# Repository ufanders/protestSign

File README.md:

protestSign
===========

A 25x7 pixel scanned-matrix display using 10mm LEDs

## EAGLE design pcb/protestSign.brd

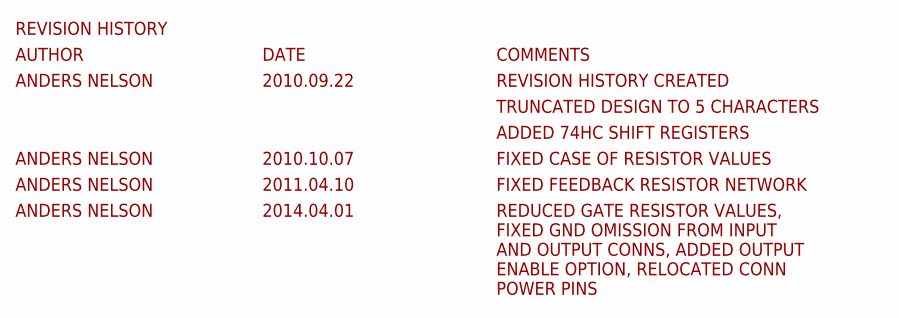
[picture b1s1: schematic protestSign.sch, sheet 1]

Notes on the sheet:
REVISION HISTORY
AUTHOR
DATE
COMMENTS
ANDERS NELSON
2010.09.22
REVISION HISTORY CREATED
TRUNCATED DESIGN TO 5 CHARACTERS
ADDED 74HC SHIFT REGISTERS
2010.10.07
FIXED CASE OF RESISTOR VALUES
2011.04.10
FIXED FEEDBACK RESISTOR NETWORK
2014.04.01
REDUCED GATE RESISTOR VALUES, FIXED GND OMISSION FROM INPUT AND OUTPUT CONNS, ADDED OUTPUT ENABLE OPTION, RELOCATED CONN POWER PINS

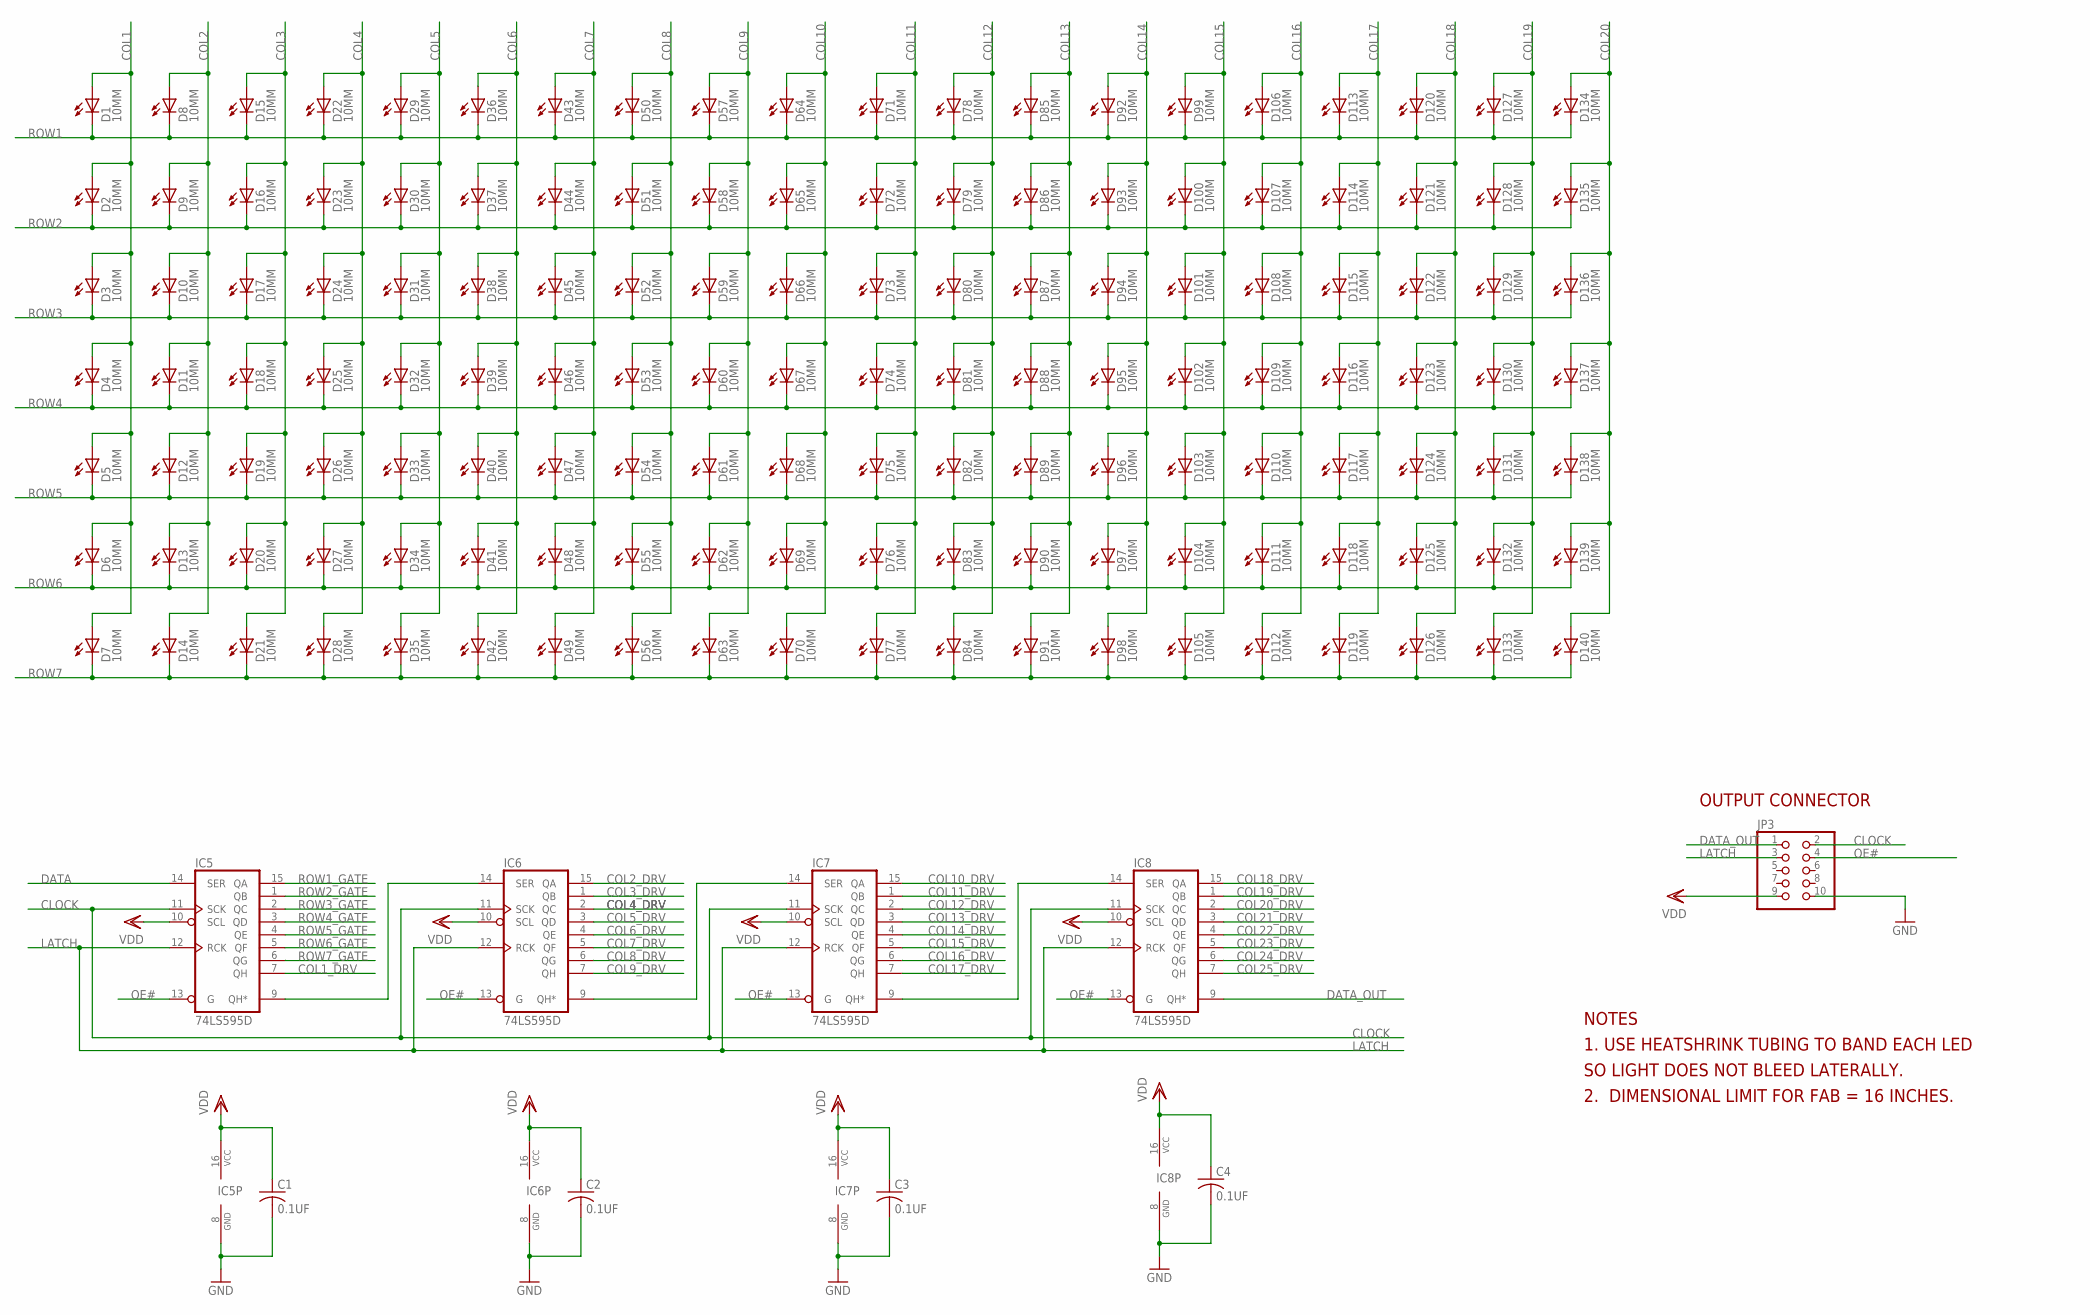
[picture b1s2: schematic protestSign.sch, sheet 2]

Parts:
C1, C2, C3, C4: 0.1UF; C0603
D1, D2, D3, D4, D5, D6, D7, D8, D9, D10, D11, D12, D13, D14, D15, D16, D17, D18, D19, D20, D21, D22, D23, D24, D25, D26, D27, D28, D29, D30, D31, D32, D33, D34, D35, D36, D37, D38, D39, D40, D41, D42, D43, D44, D45, D46, D47, D48, D49, D50, D51, D52, D53, D54, D55, D56, D57, D58, D59, D60, D61, D62, D63, D64, D65, D66, D67, D68, D69, D70, D71, D72, D73, D74, D75, D76, D77, D78, D79, D80, D81, D82, D83, D84, D85, D86, D87, D88, D89, D90, D91, D92, D93, D94, D95, D96, D97, D98, D99, D100, D101, D102, D103, D104, D105, D106, D107, D108, D109, D110, D111, D112, D113, D114, D115, D116, D117, D118, D119, D120, D121, D122, D123, D124, D125, D126, D127, D128, D129, D130, D131, D132, D133, D134, D135, D136, D137, D138, D139, D140: 10MM; LED_10MM
IC5, IC6, IC7, IC8: 74LS595D; SO16
JP3: PINHD-2X5; 2X05

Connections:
CLOCK: IC5.11 (SCK), IC6.11 (SCK), IC7.11 (SCK), IC8.11 (SCK), JP3.2; also elsewhere on the board
COL1: D1.A, D2.A, D3.A, D4.A, D5.A, D6.A, D7.A; also elsewhere on the board
COL1_DRV: IC5.7 (QH); also elsewhere on the board
COL2: D8.A, D9.A, D10.A, D11.A, D12.A, D13.A, D14.A; also elsewhere on the board
COL2_DRV: IC6.15 (QA); also elsewhere on the board
COL3: D15.A, D16.A, D17.A, D18.A, D19.A, D20.A, D21.A; also elsewhere on the board
COL3_DRV: IC6.1 (QB); also elsewhere on the board
COL4: D22.A, D23.A, D24.A, D25.A, D26.A, D27.A, D28.A; also elsewhere on the board
COL4_DRV: IC6.2 (QC); also elsewhere on the board
COL5: D29.A, D30.A, D31.A, D32.A, D33.A, D34.A, D35.A; also elsewhere on the board
COL5_DRV: IC6.3 (QD); also elsewhere on the board
COL6: D36.A, D37.A, D38.A, D39.A, D40.A, D41.A, D42.A; also elsewhere on the board
COL6_DRV: IC6.4 (QE); also elsewhere on the board
COL7: D43.A, D44.A, D45.A, D46.A, D47.A, D48.A, D49.A; also elsewhere on the board
COL7_DRV: IC6.5 (QF); also elsewhere on the board
COL8: D50.A, D51.A, D52.A, D53.A, D54.A, D55.A, D56.A; also elsewhere on the board
COL8_DRV: IC6.6 (QG); also elsewhere on the board
COL9: D57.A, D58.A, D59.A, D60.A, D61.A, D62.A, D63.A; also elsewhere on the board
COL9_DRV: IC6.7 (QH); also elsewhere on the board
COL10: D64.A, D65.A, D66.A, D67.A, D68.A, D69.A, D70.A; also elsewhere on the board
COL10_DRV: IC7.15 (QA); also elsewhere on the board
COL11: D71.A, D72.A, D73.A, D74.A, D75.A, D76.A, D77.A; also elsewhere on the board
COL11_DRV: IC7.1 (QB); also elsewhere on the board
COL12: D78.A, D79.A, D80.A, D81.A, D82.A, D83.A, D84.A; also elsewhere on the board
COL12_DRV: IC7.2 (QC); also elsewhere on the board
COL13: D85.A, D86.A, D87.A, D88.A, D89.A, D90.A, D91.A; also elsewhere on the board
COL13_DRV: IC7.3 (QD); also elsewhere on the board
COL14: D92.A, D93.A, D94.A, D95.A, D96.A, D97.A, D98.A; also elsewhere on the board
COL14_DRV: IC7.4 (QE); also elsewhere on the board
COL15: D99.A, D100.A, D101.A, D102.A, D103.A, D104.A, D105.A; also elsewhere on the board
COL15_DRV: IC7.5 (QF); also elsewhere on the board
COL16: D106.A, D107.A, D108.A, D109.A, D110.A, D111.A, D112.A; also elsewhere on the board
COL16_DRV: IC7.6 (QG); also elsewhere on the board
COL17: D113.A, D114.A, D115.A, D116.A, D117.A, D118.A, D119.A; also elsewhere on the board
COL17_DRV: IC7.7 (QH); also elsewhere on the board
COL18: D120.A, D121.A, D122.A, D123.A, D124.A, D125.A, D126.A; also elsewhere on the board
COL18_DRV: IC8.15 (QA); also elsewhere on the board
COL19: D127.A, D128.A, D129.A, D130.A, D131.A, D132.A, D133.A; also elsewhere on the board
COL19_DRV: IC8.1 (QB); also elsewhere on the board
COL20: D134.A, D135.A, D136.A, D137.A, D138.A, D139.A, D140.A; also elsewhere on the board
COL20_DRV: IC8.2 (QC); also elsewhere on the board
COL21_DRV: IC8.3 (QD); also elsewhere on the board
COL22_DRV: IC8.4 (QE); also elsewhere on the board
COL23_DRV: IC8.5 (QF); also elsewhere on the board
COL24_DRV: IC8.6 (QG); also elsewhere on the board
COL25_DRV: IC8.7 (QH); also elsewhere on the board
DATA: IC5.14 (SER); also elsewhere on the board
DATA_OUT: IC8.9 (QH*), JP3.1
GND: C1.2, C2.2, C3.2, C4.2, IC5.8 (GND), IC6.8 (GND), IC7.8 (GND), IC8.8 (GND), JP3.10; also elsewhere on the board
LATCH: IC5.12 (RCK), IC6.12 (RCK), IC7.12 (RCK), IC8.12 (RCK), JP3.3; also elsewhere on the board
unnamed: IC5.9 (QH*), IC6.14 (SER)
unnamed: IC6.9 (QH*), IC7.14 (SER)
unnamed: IC7.9 (QH*), IC8.14 (SER)
OE#: IC5.13 (G), IC6.13 (G), IC7.13 (G), IC8.13 (G), JP3.4; also elsewhere on the board
ROW1: D1.C, D8.C, D15.C, D22.C, D29.C, D36.C, D43.C, D50.C, D57.C, D64.C, D71.C, D78.C, D85.C, D92.C, D99.C, D106.C, D113.C, D120.C, D127.C, D134.C; also elsewhere on the board
ROW1_GATE: IC5.15 (QA); also elsewhere on the board
ROW2: D2.C, D9.C, D16.C, D23.C, D30.C, D37.C, D44.C, D51.C, D58.C, D65.C, D72.C, D79.C, D86.C, D93.C, D100.C, D107.C, D114.C, D121.C, D128.C, D135.C; also elsewhere on the board
ROW2_GATE: IC5.1 (QB); also elsewhere on the board
ROW3: D3.C, D10.C, D17.C, D24.C, D31.C, D38.C, D45.C, D52.C, D59.C, D66.C, D73.C, D80.C, D87.C, D94.C, D101.C, D108.C, D115.C, D122.C, D129.C, D136.C; also elsewhere on the board
ROW3_GATE: IC5.2 (QC); also elsewhere on the board
ROW4: D4.C, D11.C, D18.C, D25.C, D32.C, D39.C, D46.C, D53.C, D60.C, D67.C, D74.C, D81.C, D88.C, D95.C, D102.C, D109.C, D116.C, D123.C, D130.C, D137.C; also elsewhere on the board
ROW4_GATE: IC5.3 (QD); also elsewhere on the board
ROW5: D5.C, D12.C, D19.C, D26.C, D33.C, D40.C, D47.C, D54.C, D61.C, D68.C, D75.C, D82.C, D89.C, D96.C, D103.C, D110.C, D117.C, D124.C, D131.C, D138.C; also elsewhere on the board
ROW5_GATE: IC5.4 (QE); also elsewhere on the board
ROW6: D6.C, D13.C, D20.C, D27.C, D34.C, D41.C, D48.C, D55.C, D62.C, D69.C, D76.C, D83.C, D90.C, D97.C, D104.C, D111.C, D118.C, D125.C, D132.C, D139.C; also elsewhere on the board
ROW6_GATE: IC5.5 (QF); also elsewhere on the board
ROW7: D7.C, D14.C, D21.C, D28.C, D35.C, D42.C, D49.C, D56.C, D63.C, D70.C, D77.C, D84.C, D91.C, D98.C, D105.C, D112.C, D119.C, D126.C, D133.C, D140.C; also elsewhere on the board
ROW7_GATE: IC5.6 (QG); also elsewhere on the board
VDD: C1.1, C2.1, C3.1, C4.1, IC5.10 (SCL), IC5.16 (VCC), IC6.10 (SCL), IC6.16 (VCC), IC7.10 (SCL), IC7.16 (VCC), IC8.10 (SCL), IC8.16 (VCC), JP3.9; also elsewhere on the board

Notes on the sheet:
NOTES
1. USE HEATSHRINK TUBING TO BAND EACH LED
SO LIGHT DOES NOT BLEED LATERALLY.
2. DIMENSIONAL LIMIT FOR FAB = 16 INCHES.
OUTPUT CONNECTOR

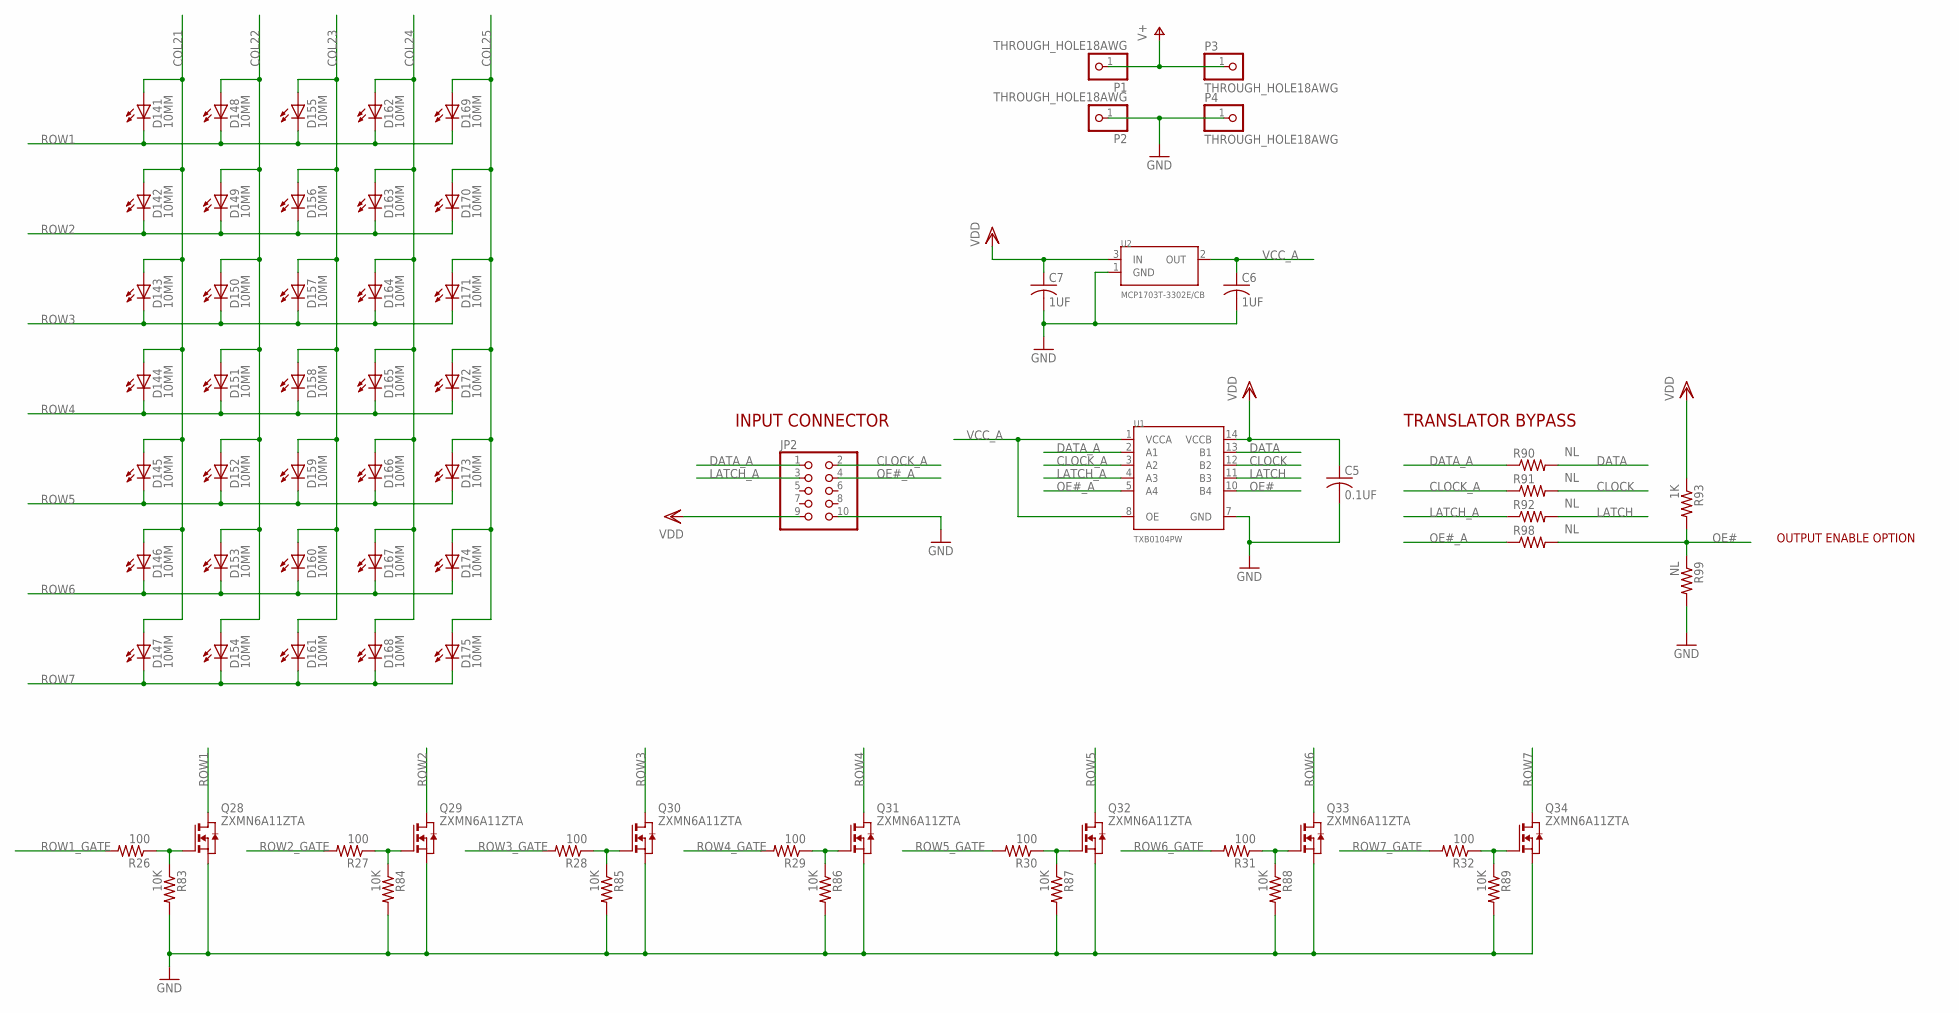
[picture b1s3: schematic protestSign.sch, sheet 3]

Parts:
C5: 0.1UF; C0603
C6, C7: 1UF; C0603
D141, D142, D143, D144, D145, D146, D147, D148, D149, D150, D151, D152, D153, D154, D155, D156, D157, D158, D159, D160, D161, D162, D163, D164, D165, D166, D167, D168, D169, D170, D171, D172, D173, D174, D175: 10MM; LED_10MM
JP2: PINHD-2X5; 2X05
P1, P2, P3, P4: THROUGH_HOLE18AWG; 18AWG_TH
Q28, Q29, Q30, Q31, Q32, Q33, Q34: ZXMN6A11ZTA; SOT89
R26, R27, R28, R29, R30, R31, R32: 100; R0603
R83, R84, R85, R86, R87, R88, R89: 10K; R0603
R90, R91, R92, R98, R99: NL; R0603
R93: 1K; R0603
U1: TXB0104PW; TSSOP14
U2: MCP1703T-3302E/CB; SOT23

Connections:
CLOCK: R91.2, U1.12 (B2); also elsewhere on the board
CLOCK_A: JP2.2, R91.1, U1.3 (A2)
COL21: D141.A, D142.A, D143.A, D144.A, D145.A, D146.A, D147.A; also elsewhere on the board
COL22: D148.A, D149.A, D150.A, D151.A, D152.A, D153.A, D154.A; also elsewhere on the board
COL23: D155.A, D156.A, D157.A, D158.A, D159.A, D160.A, D161.A; also elsewhere on the board
COL24: D162.A, D163.A, D164.A, D165.A, D166.A, D167.A, D168.A; also elsewhere on the board
COL25: D169.A, D170.A, D171.A, D172.A, D173.A, D174.A, D175.A; also elsewhere on the board
DATA: R90.2, U1.13 (B1); also elsewhere on the board
DATA_A: JP2.1, R90.1, U1.2 (A1)
GND: C5.2, C6.2, C7.2, JP2.10, P2.1, P4.1, Q28.3 (S), Q29.3 (S), Q30.3 (S), Q31.3 (S), Q32.3 (S), Q33.3 (S), Q34.3 (S), R83.2, R84.2, R85.2, R86.2, R87.2, R88.2, R89.2, R99.2, U1.7 (GND), U2.1 (GND); also elsewhere on the board
LATCH: R92.2, U1.11 (B3); also elsewhere on the board
LATCH_A: JP2.3, R92.1, U1.4 (A3)
unnamed: Q34.1 (G), R32.1, R89.1
unnamed: Q33.1 (G), R31.1, R88.1
unnamed: Q32.1 (G), R30.1, R87.1
unnamed: Q31.1 (G), R29.1, R86.1
unnamed: Q30.1 (G), R28.1, R85.1
unnamed: Q29.1 (G), R27.1, R84.1
unnamed: Q28.1 (G), R26.1, R83.1
OE#: R93.2, R98.2, R99.1, U1.10 (B4); also elsewhere on the board
OE#_A: JP2.4, R98.1, U1.5 (A4)
ROW1: D141.C, D148.C, D155.C, D162.C, D169.C, Q28.2 (D); also elsewhere on the board
ROW1_GATE: R26.2; also elsewhere on the board
ROW2: D142.C, D149.C, D156.C, D163.C, D170.C, Q29.2 (D); also elsewhere on the board
ROW2_GATE: R27.2; also elsewhere on the board
ROW3: D143.C, D150.C, D157.C, D164.C, D171.C, Q30.2 (D); also elsewhere on the board
ROW3_GATE: R28.2; also elsewhere on the board
ROW4: D144.C, D151.C, D158.C, D165.C, D172.C, Q31.2 (D); also elsewhere on the board
ROW4_GATE: R29.2; also elsewhere on the board
ROW5: D145.C, D152.C, D159.C, D166.C, D173.C, Q32.2 (D); also elsewhere on the board
ROW5_GATE: R30.2; also elsewhere on the board
ROW6: D146.C, D153.C, D160.C, D167.C, D174.C, Q33.2 (D); also elsewhere on the board
ROW6_GATE: R31.2; also elsewhere on the board
ROW7: D147.C, D154.C, D161.C, D168.C, D175.C, Q34.2 (D); also elsewhere on the board
ROW7_GATE: R32.2; also elsewhere on the board
V+: P1.1, P3.1; also elsewhere on the board
VCC_A: C6.1, U1.1 (VCCA), U1.8 (OE), U2.2 (OUT)
VDD: C5.1, C7.1, JP2.9, R93.1, U1.14 (VCCB), U2.3 (IN); also elsewhere on the board

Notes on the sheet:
TRANSLATOR BYPASS
INPUT CONNECTOR
OUTPUT ENABLE OPTION

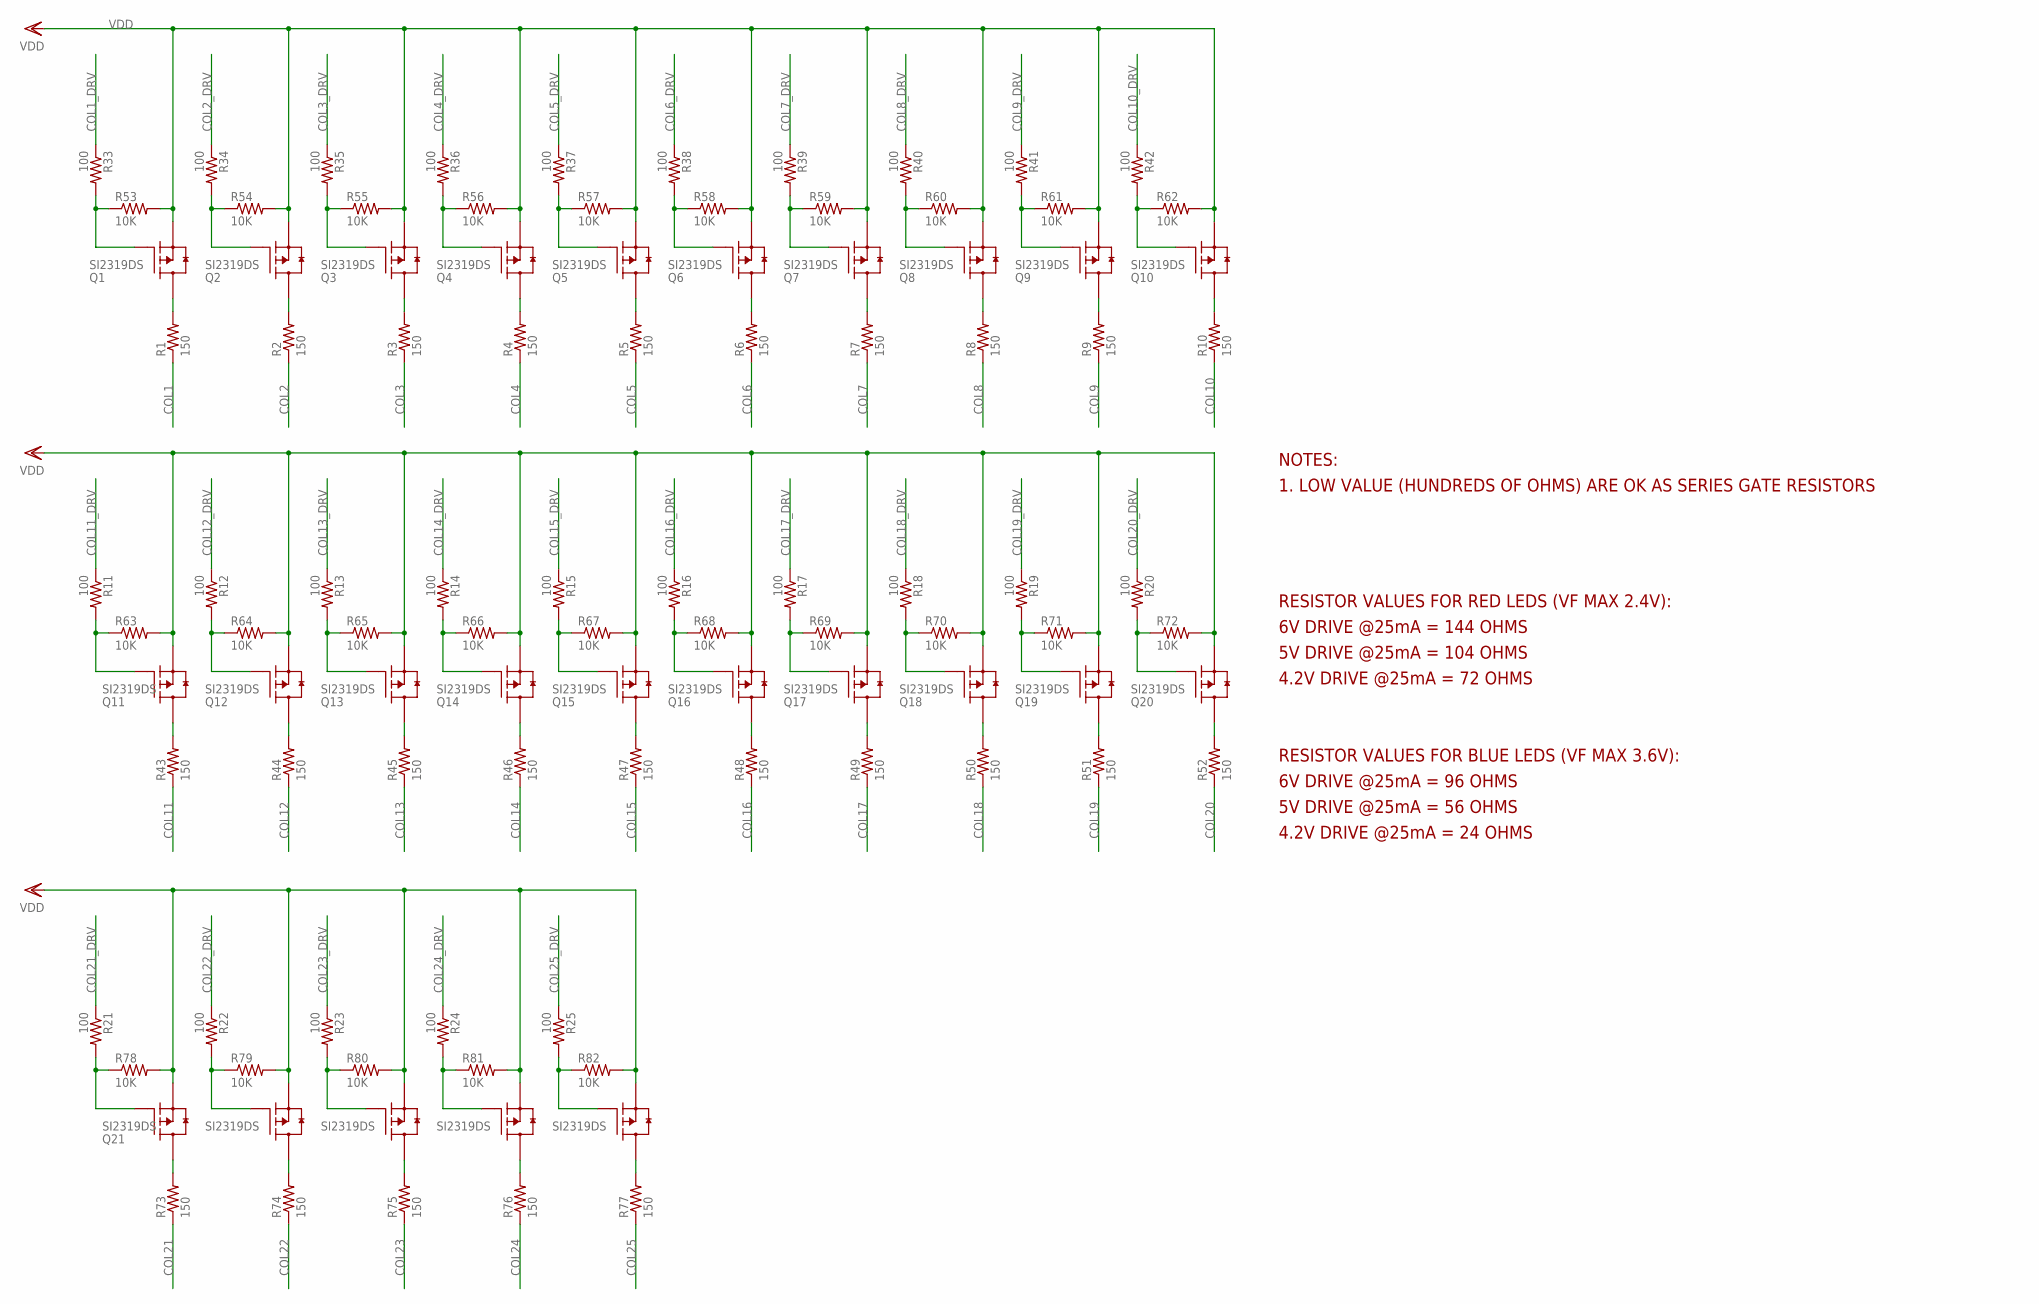
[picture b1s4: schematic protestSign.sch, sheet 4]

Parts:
Q1, Q2, Q3, Q4, Q5, Q6, Q7, Q8, Q9, Q10, Q11, Q12, Q13, Q14, Q15, Q16, Q17, Q18, Q19, Q20, Q21, Q22, Q23, Q24, Q25: SI2319DS; SOT23
R1, R2, R3, R4, R5, R6, R7, R8, R9, R10, R43, R44, R45, R46, R47, R48, R49, R50, R51, R52, R73, R74, R75, R76, R77: 150; M0805
R11, R12, R13, R14, R15, R16, R17, R18, R19, R20, R21, R22, R23, R24, R25, R33, R34, R35, R36, R37, R38, R39, R40, R41, R42: 100; R0603
R53, R54, R55, R56, R57, R58, R59, R60, R61, R62, R63, R64, R65, R66, R67, R68, R69, R70, R71, R72, R78, R79, R80, R81, R82: 10K; R0603

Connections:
COL1: R1.1; also elsewhere on the board
COL1_DRV: R33.1; also elsewhere on the board
COL2: R2.1; also elsewhere on the board
COL2_DRV: R34.1; also elsewhere on the board
COL3: R3.1; also elsewhere on the board
COL3_DRV: R35.1; also elsewhere on the board
COL4: R4.1; also elsewhere on the board
COL4_DRV: R36.1; also elsewhere on the board
COL5: R5.1; also elsewhere on the board
COL5_DRV: R37.1; also elsewhere on the board
COL6: R6.1; also elsewhere on the board
COL6_DRV: R38.1; also elsewhere on the board
COL7: R7.1; also elsewhere on the board
COL7_DRV: R39.1; also elsewhere on the board
COL8: R8.1; also elsewhere on the board
COL8_DRV: R40.1; also elsewhere on the board
COL9: R9.1; also elsewhere on the board
COL9_DRV: R41.1; also elsewhere on the board
COL10: R10.1; also elsewhere on the board
COL10_DRV: R42.1; also elsewhere on the board
COL11: R43.1; also elsewhere on the board
COL11_DRV: R11.1; also elsewhere on the board
COL12: R44.1; also elsewhere on the board
COL12_DRV: R12.1; also elsewhere on the board
COL13: R45.1; also elsewhere on the board
COL13_DRV: R13.1; also elsewhere on the board
COL14: R46.1; also elsewhere on the board
COL14_DRV: R14.1; also elsewhere on the board
COL15: R47.1; also elsewhere on the board
COL15_DRV: R15.1; also elsewhere on the board
COL16: R48.1; also elsewhere on the board
COL16_DRV: R16.1; also elsewhere on the board
COL17: R49.1; also elsewhere on the board
COL17_DRV: R17.1; also elsewhere on the board
COL18: R50.1; also elsewhere on the board
COL18_DRV: R18.1; also elsewhere on the board
COL19: R51.1; also elsewhere on the board
COL19_DRV: R19.1; also elsewhere on the board
COL20: R52.1; also elsewhere on the board
COL20_DRV: R20.1; also elsewhere on the board
COL21: R73.1; also elsewhere on the board
COL21_DRV: R21.1; also elsewhere on the board
COL22: R74.1; also elsewhere on the board
COL22_DRV: R22.1; also elsewhere on the board
COL23: R75.1; also elsewhere on the board
COL23_DRV: R23.1; also elsewhere on the board
COL24: R76.1; also elsewhere on the board
COL24_DRV: R24.1; also elsewhere on the board
COL25: R77.1; also elsewhere on the board
COL25_DRV: R25.1; also elsewhere on the board
unnamed: Q1.1 (G), R33.2, R53.1
unnamed: Q11.1 (G), R11.2, R63.1
unnamed: Q2.1 (G), R34.2, R54.1
unnamed: Q12.1 (G), R12.2, R64.1
unnamed: Q13.1 (G), R13.2, R65.1
unnamed: Q14.1 (G), R14.2, R66.1
unnamed: Q15.1 (G), R15.2, R67.1
unnamed: Q16.1 (G), R16.2, R68.1
unnamed: Q17.1 (G), R17.2, R69.1
unnamed: Q18.1 (G), R18.2, R70.1
unnamed: Q19.1 (G), R19.2, R71.1
unnamed: Q20.1 (G), R20.2, R72.1
unnamed: Q11.3 (D), R43.2
unnamed: Q12.3 (D), R44.2
unnamed: Q13.3 (D), R45.2
unnamed: Q14.3 (D), R46.2
unnamed: Q15.3 (D), R47.2
unnamed: Q16.3 (D), R48.2
unnamed: Q17.3 (D), R49.2
unnamed: Q18.3 (D), R50.2
unnamed: Q19.3 (D), R51.2
unnamed: Q20.3 (D), R52.2
unnamed: Q21.1 (G), R21.2, R78.1
unnamed: Q22.1 (G), R22.2, R79.1
unnamed: Q23.1 (G), R23.2, R80.1
unnamed: Q24.1 (G), R24.2, R81.1
unnamed: Q25.1 (G), R25.2, R82.1
unnamed: Q21.3 (D), R73.2
unnamed: Q22.3 (D), R74.2
unnamed: Q3.1 (G), R35.2, R55.1
unnamed: Q4.1 (G), R36.2, R56.1
unnamed: Q5.1 (G), R37.2, R57.1
unnamed: Q6.1 (G), R38.2, R58.1
unnamed: Q7.1 (G), R39.2, R59.1
unnamed: Q8.1 (G), R40.2, R60.1
unnamed: Q9.1 (G), R41.2, R61.1
unnamed: Q10.1 (G), R42.2, R62.1
unnamed: Q1.3 (D), R1.2
unnamed: Q2.3 (D), R2.2
unnamed: Q3.3 (D), R3.2
unnamed: Q4.3 (D), R4.2
unnamed: Q5.3 (D), R5.2
unnamed: Q6.3 (D), R6.2
unnamed: Q7.3 (D), R7.2
unnamed: Q8.3 (D), R8.2
unnamed: Q9.3 (D), R9.2
unnamed: Q10.3 (D), R10.2
unnamed: Q23.3 (D), R75.2
unnamed: Q24.3 (D), R76.2
unnamed: Q25.3 (D), R77.2
VDD: Q1.2 (S), Q2.2 (S), Q3.2 (S), Q4.2 (S), Q5.2 (S), Q6.2 (S), Q7.2 (S), Q8.2 (S), Q9.2 (S), Q10.2 (S), Q11.2 (S), Q12.2 (S), Q13.2 (S), Q14.2 (S), Q15.2 (S), Q16.2 (S), Q17.2 (S), Q18.2 (S), Q19.2 (S), Q20.2 (S), Q21.2 (S), Q22.2 (S), Q23.2 (S), Q24.2 (S), Q25.2 (S), R53.2, R54.2, R55.2, R56.2, R57.2, R58.2, R59.2, R60.2, R61.2, R62.2, R63.2, R64.2, R65.2, R66.2, R67.2, R68.2, R69.2, R70.2, R71.2, R72.2, R78.2, R79.2, R80.2, R81.2, R82.2; also elsewhere on the board

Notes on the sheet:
NOTES:
1. LOW VALUE (HUNDREDS OF OHMS) ARE OK AS SERIES GATE RESISTORS
RESISTOR VALUES FOR RED LEDS (VF MAX 2.4V):
RESISTOR VALUES FOR BLUE LEDS (VF MAX 3.6V):
6V DRIVE @25mA = 144 OHMS
5V DRIVE @25mA = 104 OHMS
4.2V DRIVE @25mA = 72 OHMS
6V DRIVE @25mA = 96 OHMS
5V DRIVE @25mA = 56 OHMS
4.2V DRIVE @25mA = 24 OHMS

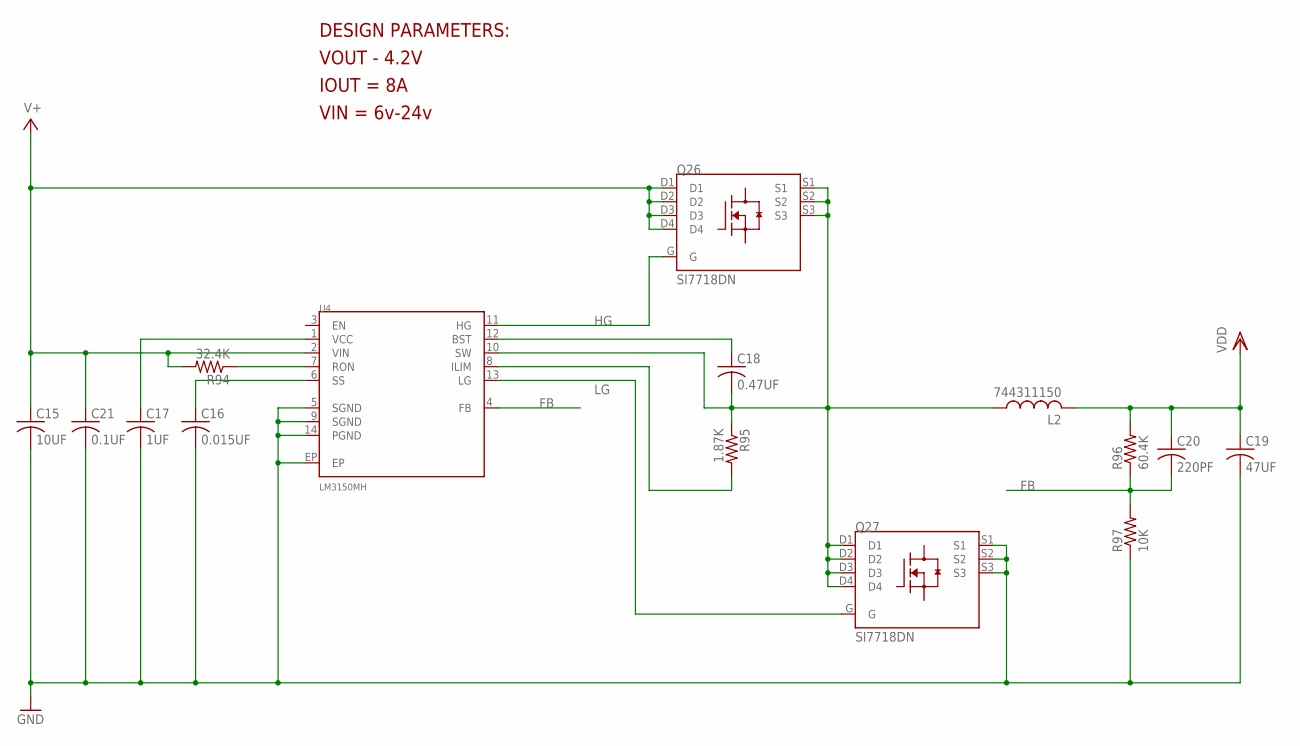
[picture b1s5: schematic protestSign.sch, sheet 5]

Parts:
C15: 10UF; C1210
C16: 0.015UF; C0603
C17: 1UF; C0603
C18: 0.47UF; C0603
C19: 47UF; C1210
C20: 220PF; C0603
C21: 0.1UF; C0603
L2: 744311150
Q26, Q27: SI7718DN; POWERPAK_1212_8
R94: 32.4K; R0603
R95: 1.87K; R0603
R96: 60.4K; R0603
R97: 10K; R0603
U4: LM3150MH; TSSOP14_EP

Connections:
FB: C20.2, R96.1, R97.2, U4.4 (FB)
GND: C15.2, C16.2, C17.2, C19.2, C21.2, Q27.S1, Q27.S2, Q27.S3, R97.1, U4.5 (SGND), U4.9 (SGND), U4.14 (PGND), U4.EP; also elsewhere on the board
HG: Q26.G, U4.11 (HG)
LG: Q27.G, U4.13 (LG)
unnamed: R94.1, U4.7 (RON)
unnamed: C16.1, U4.6 (SS)
unnamed: C17.1, U4.1 (VCC)
unnamed: C18.1, U4.12 (BST)
unnamed: R95.2, U4.8 (ILIM)
SW: C18.2, L2.P$1 (1), Q26.S1, Q26.S2, Q26.S3, Q27.D1, Q27.D2, Q27.D3, Q27.D4, R95.1, U4.10 (SW)
V+: C15.1, C21.1, Q26.D1, Q26.D2, Q26.D3, Q26.D4, R94.2, U4.2 (VIN); also elsewhere on the board
VDD: C19.1, C20.1, L2.P$2 (2), R96.2; also elsewhere on the board

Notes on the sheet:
DESIGN PARAMETERS:
VOUT - 4.2V
IOUT = 8A
VIN = 6v-24v

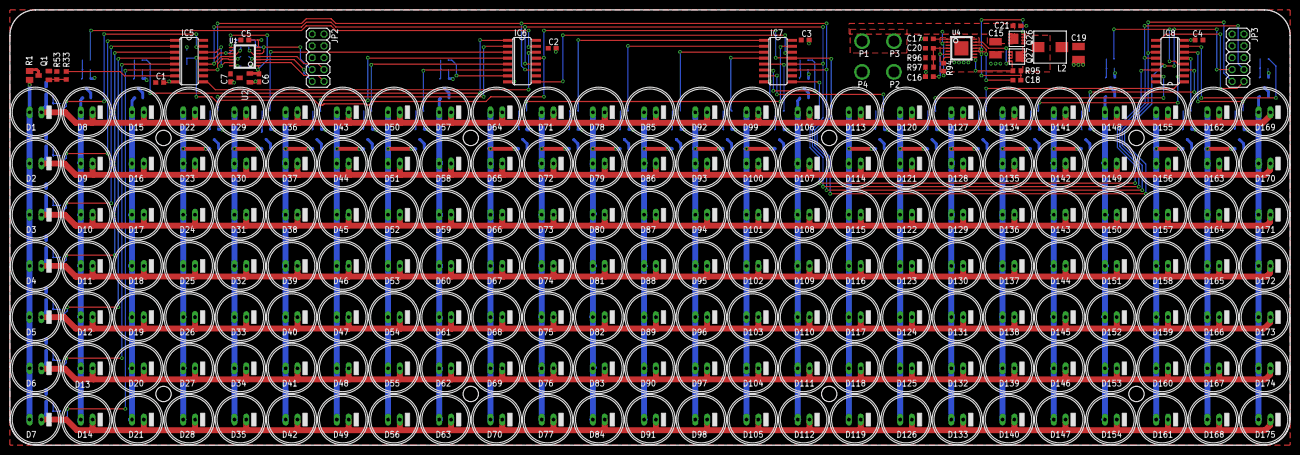
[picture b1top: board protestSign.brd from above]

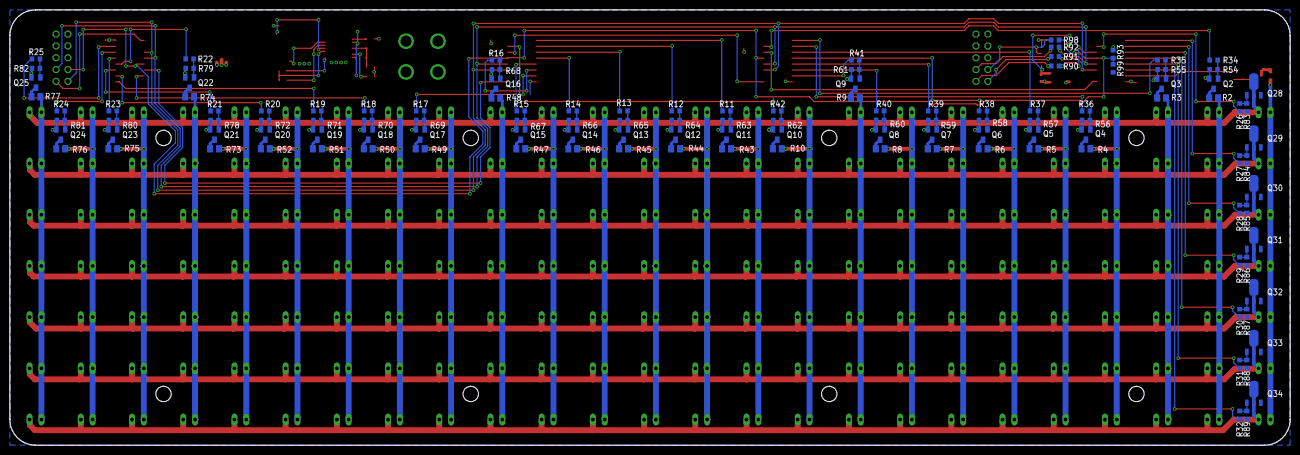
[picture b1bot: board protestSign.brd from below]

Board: 2 copper layers, 275.0 x 93.5 mm, 336 parts (123 on the bottom side), 146 nets.

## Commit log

2014-04-02 Buttoned up stuff and fixed a few things
    -Fixed connector signals.
    -Added output enable option with pullup/pulldown.
    -Updated silkscreen.
2014-04-02 Added .gitignore
2014-04-02 Removed scratch files.
2014-04-08 Imported firmware
    -Builds and runs well.
2014-08-01 Updated OS-specific XML crap.

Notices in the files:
pcb/protestSign.brd:
(C) 2010 ANDERS K NELSON
